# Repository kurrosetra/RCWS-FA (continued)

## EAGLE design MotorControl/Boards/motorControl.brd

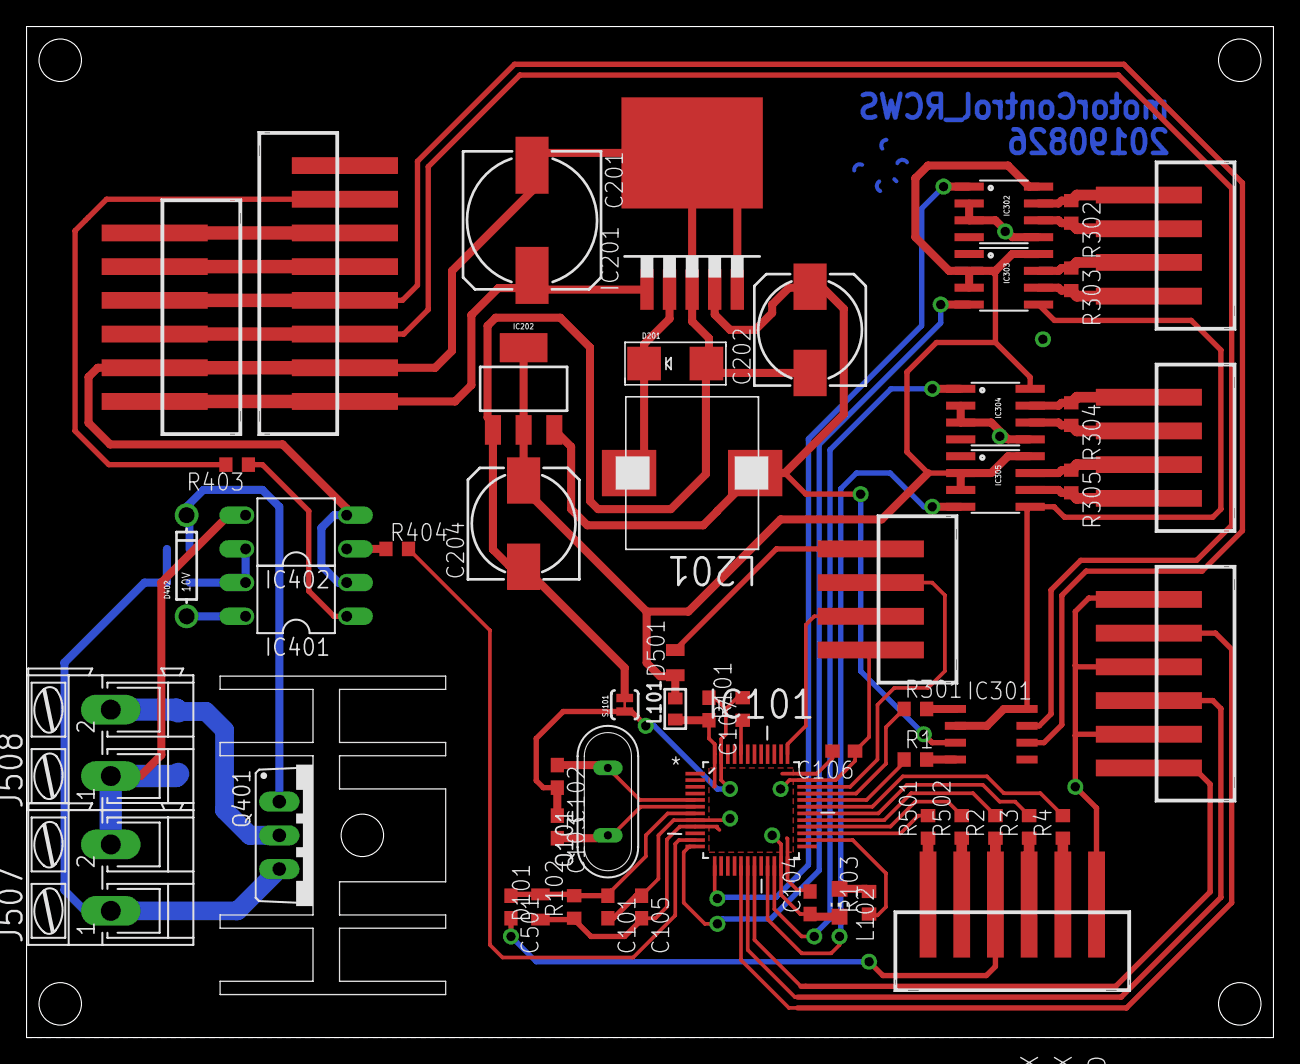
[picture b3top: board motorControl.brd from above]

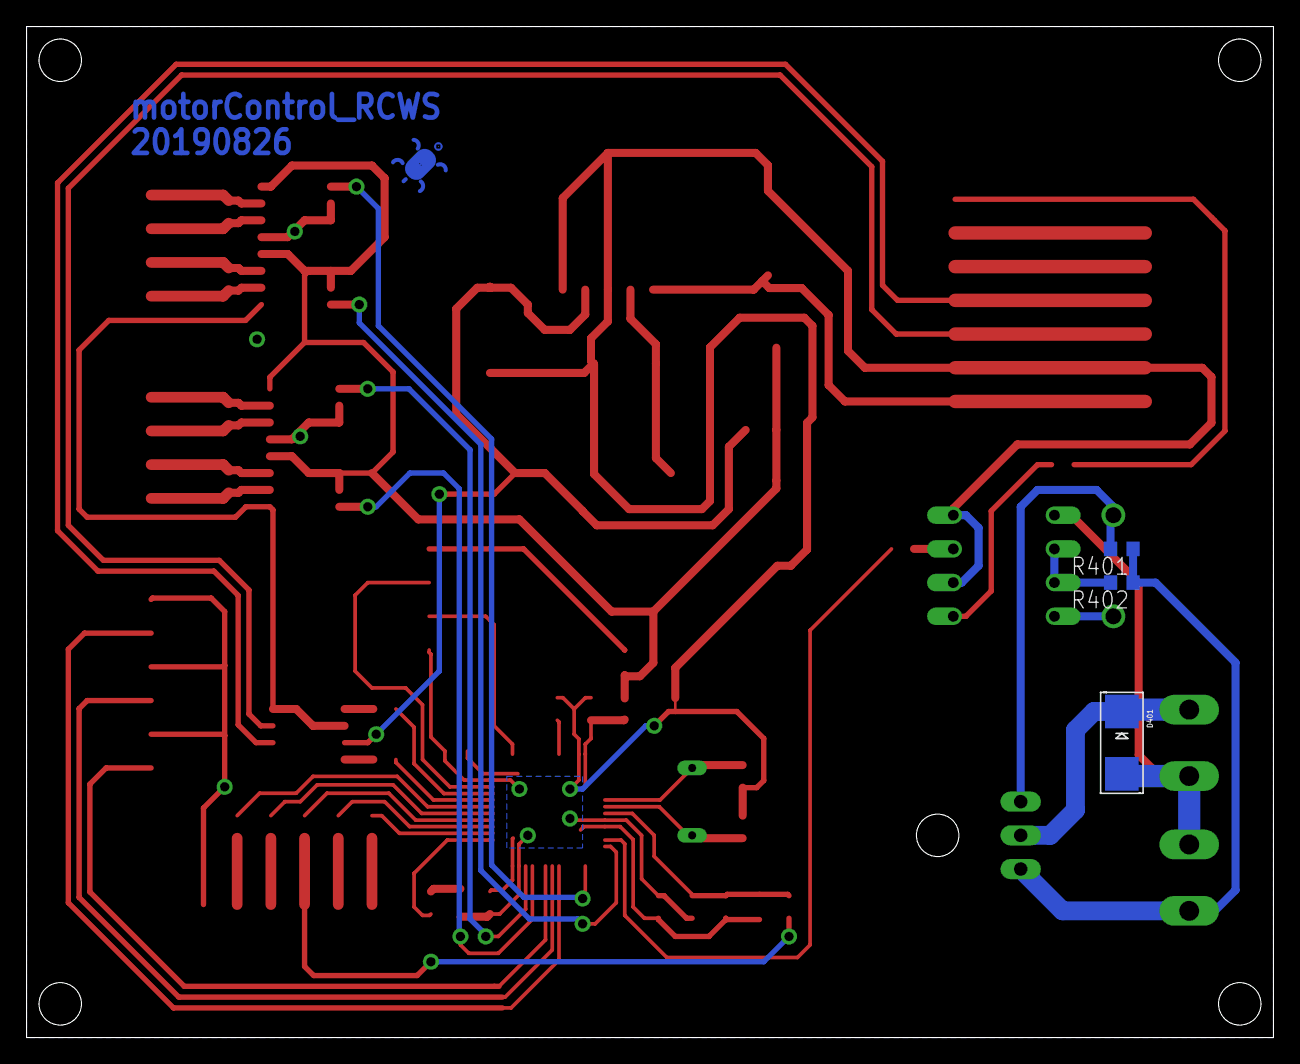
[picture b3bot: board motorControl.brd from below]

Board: 2 copper layers, 94.0 x 76.2 mm, 61 parts (3 on the bottom side), 59 nets.

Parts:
C101: 10n; C0603
C102, C103: 22p; C0603
C104, C105, C106, C107, C501: 100n; C0603
C201: 470u/35V; 153CLV-1012
C202, C204: 1000u/6V3; 153CLV-0810
D101, D501: SCHOTTKY; MICROMELF-W
D201, D401: SS34; SMADIODE
D402: 10V; DO-4148
IC101: STM32F103C8T6; QFP50P900X900X160-48N
IC201: LM2596S-5V; D2PAK
IC202: LM1117-3V3; SOT223
IC301: MCP2561-E/SN; SOIC-8
IC302, IC303, IC304, IC305: RS485SOIC; SO08
IC401, IC402: PC817; DIL04
J501: PROG; XH-4-VERT-SMD
J502: BUS; XH-8-VERT-SMD
J503: OPTRONIK; XH-6-VERT-SMD
J504: MTR_AZ_COMM; XH-4-VERT-SMD
J505: MTR_EL_COMM; XH-4-VERT-SMD
J506: LIMIT_SWITCH; XH-6-VERT-SMD
J507: POWER_IN; AK300/2
J508: TRIGGER_OUT; AK300/2
J509: COCK_DRIVER; XH-6-VERT-SMD
KK401: BV_240X170-HOLE
L101: FB_0603; L0603
L102: GREEN; CHIP-LED0805
L201: 33uH; PA4342
Q101: 8MHz; QS
Q401: IRF9530; TO220BV
R1, R2, R3, R4, R301, R302, R303, R304, R305, R501, R502: 120R; R0603
R101, R102: 100K; R0603
R103: 1k; R0603
R401: 470R; R0603
R402: 100k; R0603
R403, R404: 330R; R0603
SJ101: SJ_2S-TRACE
U$1: KURRO_FOOTPRINT; KURRO-LOGO

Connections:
+3V3: C204.+, D501.C, IC202.2, IC202.4, IC302.8, IC303.2, IC303.3, IC303.8, IC304.8, IC305.2, IC305.3, IC305.8, L101.2
+5V: C202.+, IC201.4, IC202.3, IC301.3, L201.P$2
+12V: C201.+, IC201.1, J502.1, J503.6
+24V: J507.1, Q401.S, R401.1, R402.1
AGND: C101.2, C102.2, C103.1, C104.1, C105.1, C106.1, C107.1, IC101.8, IC101.23, IC101.35, IC101.47, J501.4, L102.C, R101.2, SJ101.1
BOOT0: IC101.44, R101.1
BUS_CANH: IC301.7, J502.3, J503.4
BUS_CANL: IC301.6, J502.4, J503.3
BUS_RXD: IC101.32, R1.1
BUS_TRIGGER_PULSE: J502.7, R403.2
BUS_TXD: IC101.33, R301.1
BUS_VIDEO+: J502.5, J503.2
BUS_VIDEO-: J502.6, J503.1
COCK_ALM: IC101.31, R4.2
COCK_AWO: IC101.28, R502.2
COCK_DIR: IC101.29, R2.2
COCK_PLS: IC101.30, R3.2
COCK_POS: IC101.27, R501.2
GND: C201.-, C202.-, C204.-, D201.A, IC201.3, IC201.5, IC201.6, IC202.1, IC301.2, IC301.8, IC302.2, IC302.3, IC302.5, IC303.5, IC304.2, IC304.3, IC304.5, IC305.5, IC401.2, IC402.2, J502.2, J503.5, J506.1, J506.3, J506.5, J509.1, SJ101.2
LIM_AZ: IC101.17, J506.2
LIM_EL_DOWN: IC101.19, J506.6
LIM_EL_UP: IC101.18, J506.4
LM2596_OUT: D201.C, IC201.2, L201.P$1
MTR_AZ_RXD: IC101.13, IC302.1
MTR_AZ_RX_A: IC303.6, J504.4, R303.2
MTR_AZ_RX_B: IC303.7, J504.3, R303.1
MTR_AZ_TXD: IC101.12, IC303.4
MTR_AZ_TX_A: IC302.6, J504.2, R302.2
MTR_AZ_TX_B: IC302.7, J504.1, R302.1
MTR_EL_RXD: IC101.22, IC304.1
MTR_EL_RX_A: IC305.6, J505.4, R305.2
MTR_EL_RX_B: IC305.7, J505.3, R305.1
MTR_EL_TXD: IC101.21, IC305.4
MTR_EL_TX_A: IC304.6, J505.2, R304.2
MTR_EL_TX_B: IC304.7, J505.1, R304.1
unnamed: L102.A, R103.2
unnamed: IC101.26, R103.1
unnamed: C103.2, IC101.6, Q101.1
unnamed: C102.1, IC101.5, Q101.2
unnamed: IC301.1, R301.2
unnamed: IC301.4, R1.2
unnamed: J509.5, R502.1
unnamed: J509.6, R501.1
unnamed: C501.2, J509.4, R2.1
unnamed: J509.3, R3.1
unnamed: J509.2, R4.1
unnamed: D501.A, J501.1
unnamed: D402.C, Q401.G, R401.2
unnamed: IC401.3, IC402.4, R402.2
unnamed: IC401.1, R403.1
unnamed: IC402.1, R404.1
unnamed: D402.A, IC401.4
RST: C101.1, C501.1, D101.A, IC101.7, R102.2
SWCLK: IC101.37, J501.3
SWDIO: IC101.34, J501.2
TRIGGER+: D401.C, J508.2, Q401.D
TRIGGER_ENABLE: IC101.11, R404.2
V-: D401.A, IC402.3, J507.2, J508.1
VDD: C104.2, C105.2, C106.2, C107.2, D101.C, IC101.9, IC101.24, IC101.36, IC101.48, L101.1, R102.1

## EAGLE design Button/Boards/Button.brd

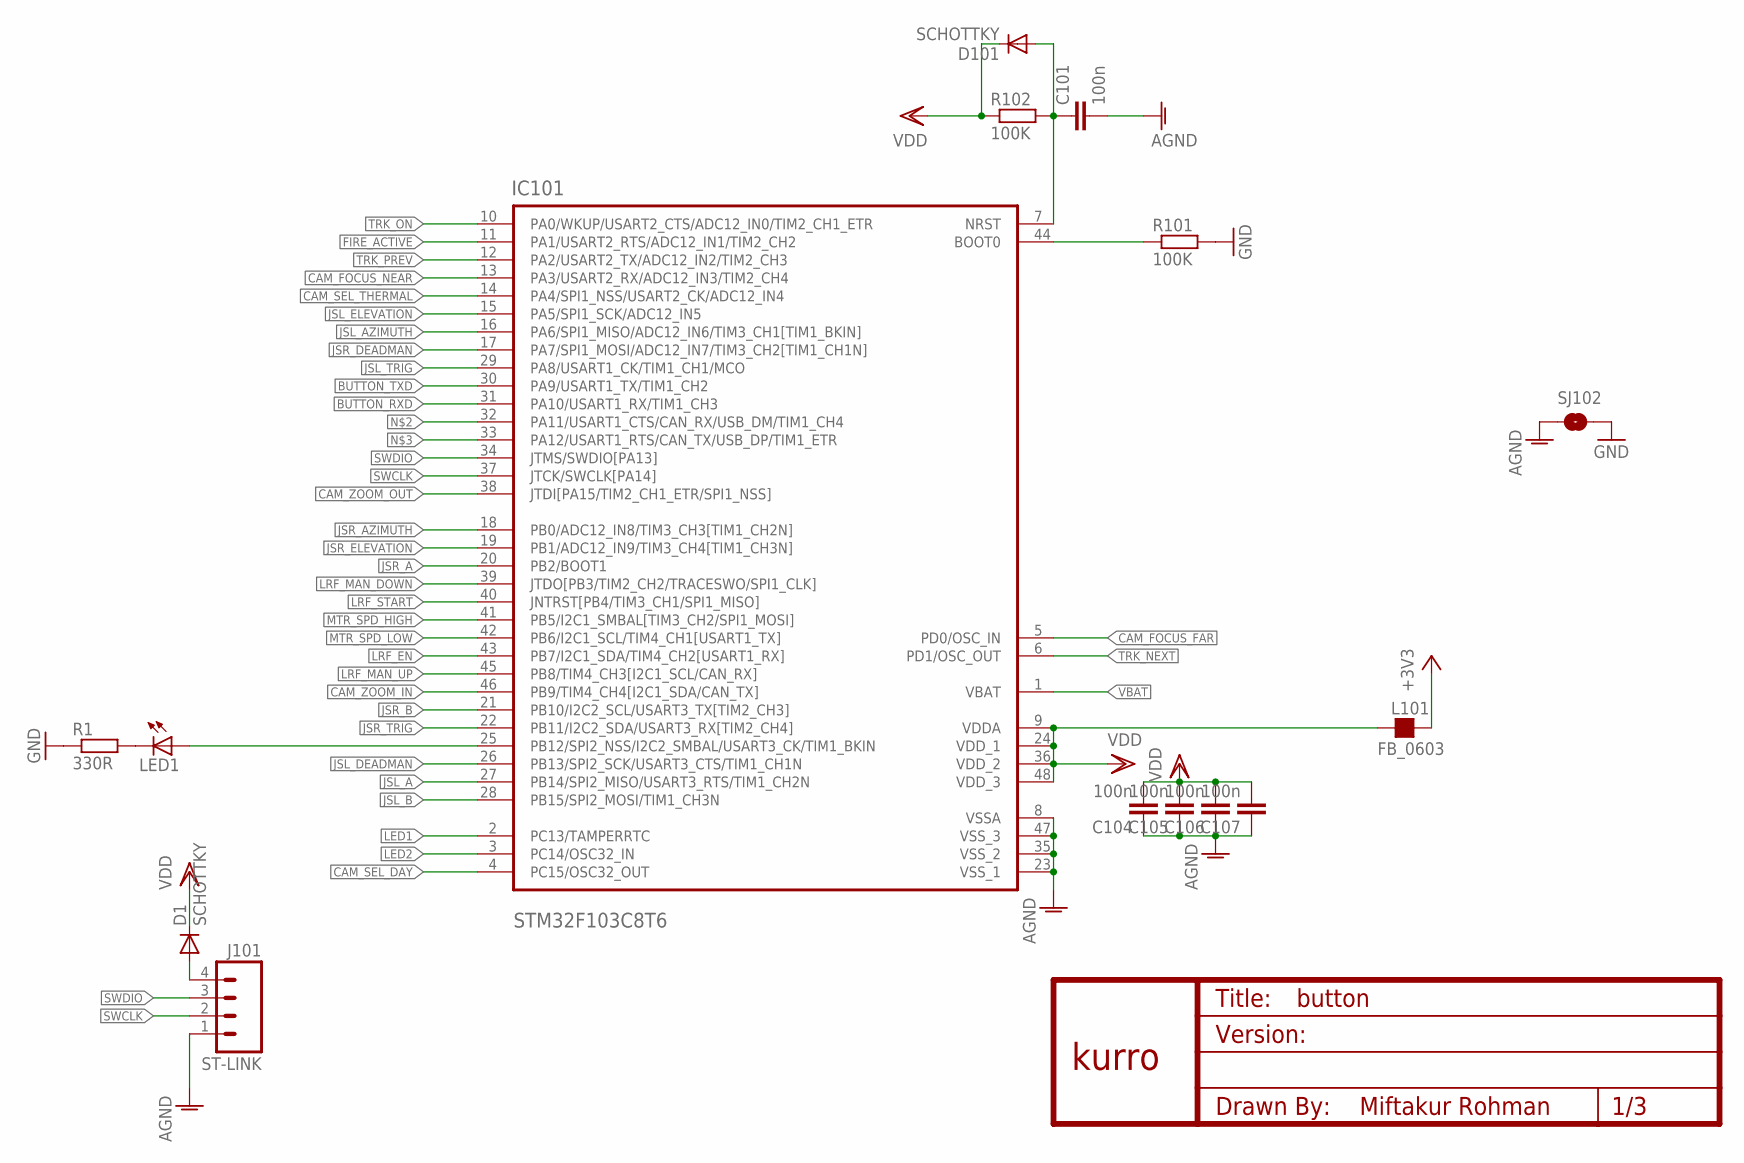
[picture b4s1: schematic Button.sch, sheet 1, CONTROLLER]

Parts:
C101, C104, C105, C106, C107: 100n; C0603
D1, D101: SCHOTTKY; MICROMELF-W
IC101: STM32F103C8T6; QFP50P900X900X160-48N
J101: ST-LINK; XH-4-VERT
L101: FB_0603; L0603
LED1: LED-3MM-NO_SILK; LED3MM-NS
R1: 330R; R0603
R101, R102: 100K; R0603
SJ102: SOLDERJUMPERTRACE; SJ_2S-TRACE
U$1: KURRO_FOOTPRINT; KURRO-LOGO

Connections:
+3V3: L101.2; also elsewhere on the board
AGND: C101.2, C104.1, C105.1, C106.1, C107.1, IC101.8 (VSSA), IC101.23 (VSS_1), IC101.35 (VSS_2), IC101.47 (VSS_3), J101.1, SJ102.1
BOOT0: IC101.44 (BOOT0), R101.1
BUTTON_RXD: IC101.31 (PA10/USART1_RX/TIM1_CH3); also elsewhere on the board
BUTTON_TXD: IC101.30 (PA9/USART1_TX/TIM1_CH2); also elsewhere on the board
CAM_FOCUS_FAR: IC101.5 (PD0/OSC_IN); also elsewhere on the board
CAM_FOCUS_NEAR: IC101.13 (PA3/USART2_RX/ADC12_IN3/TIM2_CH4); also elsewhere on the board
CAM_SEL_DAY: IC101.4 (PC15/OSC32_OUT); also elsewhere on the board
CAM_SEL_THERMAL: IC101.14 (PA4/SPI1_NSS/USART2_CK/ADC12_IN4); also elsewhere on the board
CAM_ZOOM_IN: IC101.46 (PB9/TIM4_CH4[I2C1_SDA/CAN_TX]); also elsewhere on the board
CAM_ZOOM_OUT: IC101.38 (JTDI[PA15/TIM2_CH1_ETR/SPI1_NSS]); also elsewhere on the board
FIRE_ACTIVE: IC101.11 (PA1/USART2_RTS/ADC12_IN1/TIM2_CH2); also elsewhere on the board
GND: R1.1, R101.2, SJ102.2; also elsewhere on the board
JSL_A: IC101.27 (PB14/SPI2_MISO/USART3_RTS/TIM1_CH2N); also elsewhere on the board
JSL_AZIMUTH: IC101.16 (PA6/SPI1_MISO/ADC12_IN6/TIM3_CH1[TIM1_B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); also elsewhere on the board
JSL_B: IC101.28 (PB15/SPI2_MOSI/TIM1_CH3N); also elsewhere on the board
JSL_DEADMAN: IC101.26 (PB13/SPI2_SCK/USART3_CTS/TIM1_CH1N); also elsewhere on the board
JSL_ELEVATION: IC101.15 (PA5/SPI1_SCK/ADC12_IN5); also elsewhere on the board
JSL_TRIG: IC101.29 (PA8/USART1_CK/TIM1_CH1/MCO); also elsewhere on the board
JSR_A: IC101.20 (PB2/BOOT1); also elsewhere on the board
JSR_AZIMUTH: IC101.18 (PB0/ADC12_IN8/TIM3_CH3[TIM1_CH2N]); also elsewhere on the board
JSR_B: IC101.21 (PB10/I2C2_SCL/USART3_TX[TIM2_CH3]); also elsewhere on the board
JSR_DEADMAN: IC101.17 (PA7/SPI1_MOSI/ADC12_IN7/TIM3_CH2[TIM1_C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); also elsewhere on the board
JSR_ELEVATION: IC101.19 (PB1/ADC12_IN9/TIM3_CH4[TIM1_CH3N]); also elsewhere on the board
JSR_TRIG: IC101.22 (PB11/I2C2_SDA/USART3_RX[TIM2_CH4]); also elsewhere on the board
LED1: IC101.2 (PC13/TAMPERRTC); also elsewhere on the board
LED2: IC101.3 (PC14/OSC32_IN); also elsewhere on the board
LRF_EN: IC101.43 (PB7/I2C1_SDA/TIM4_CH2[USART1_RX]); also elsewhere on the board
LRF_MAN_DOWN: IC101.39 (JTDO[PB3/TIM2_CH2/TRACESWO/SPI1_CLK]); also elsewhere on the board
LRF_MAN_UP: IC101.45 (PB8/TIM4_CH3[I2C1_SCL/CAN_RX]); also elsewhere on the board
LRF_START: IC101.40 (JNTRST[PB4/TIM3_CH1/SPI1_MISO]); also elsewhere on the board
MTR_SPD_HIGH: IC101.41 (PB5/I2C1_SMBAL[TIM3_CH2/SPI1_MOSI]); also elsewhere on the board
MTR_SPD_LOW: IC101.42 (PB6/I2C1_SCL/TIM4_CH1[USART1_TX]); also elsewhere on the board
unnamed: IC101.25 (PB12/SPI2_NSS/I2C2_SMBAL/USART3_CK/TIM1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), LED1.A
unnamed: D1.A, J101.4
unnamed: LED1.K (C), R1.2
RST: C101.1, D101.A, IC101.7 (NRST), R102.2
SWCLK: IC101.37 (JTCK/SWCLK[PA14]), J101.2
SWDIO: IC101.34 (JTMS/SWDIO[PA13]), J101.3
TRK_NEXT: IC101.6 (PD1/OSC_OUT); also elsewhere on the board
TRK_ON: IC101.10 (PA0/WKUP/USART2_CTS/ADC12_IN0/TIM2_CH1_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); also elsewhere on the board
TRK_PREV: IC101.12 (PA2/USART2_TX/ADC12_IN2/TIM2_CH3); also elsewhere on the board
VBAT: IC101.1 (VBAT)
VDD: C104.2, C105.2, C106.2, C107.2, D1.C, D101.C, IC101.9 (VDDA), IC101.24 (VDD_1), IC101.36 (VDD_2), IC101.48 (VDD_3), L101.1, R102.1

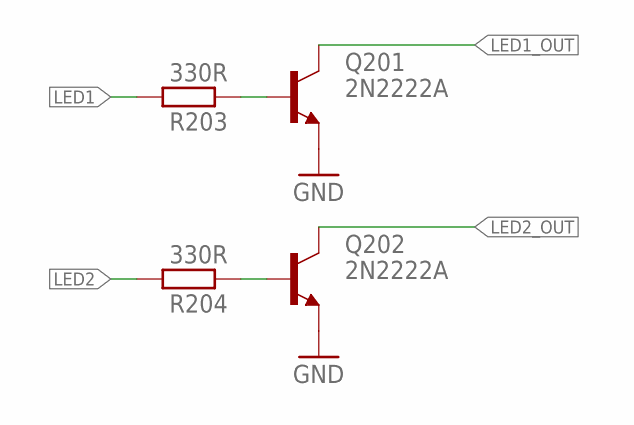
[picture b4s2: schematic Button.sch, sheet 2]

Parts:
Q201, Q202: 2N2222A; SOT23
R203, R204: 330R; R0603

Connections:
GND: Q201.2 (E), Q202.2 (E); also elsewhere on the board
LED1: R203.2; also elsewhere on the board
LED1_OUT: Q201.3 (C); also elsewhere on the board
LED2: R204.2; also elsewhere on the board
LED2_OUT: Q202.3 (C); also elsewhere on the board
unnamed: Q201.1 (B), R203.1
unnamed: Q202.1 (B), R204.1

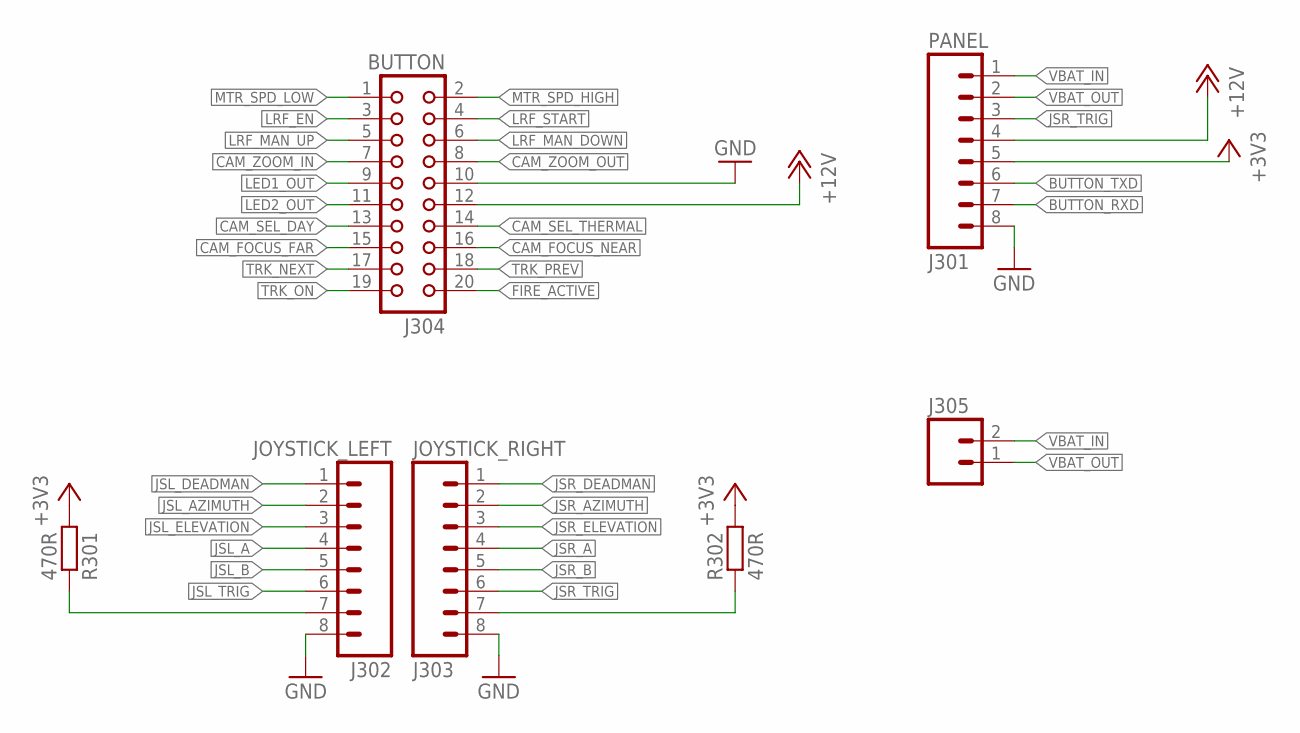
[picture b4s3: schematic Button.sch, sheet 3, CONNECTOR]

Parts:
J301: PANEL; XH-8-RA
J302: JOYSTICK_LEFT; XH-8-RA
J303: JOYSTICK_RIGHT; XH-8-RA
J304: BUTTON; CON20
J305: M02-XH-RA; XH-2-RA
R301, R302: 470R; R0603

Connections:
+3V3: J301.5, R301.2, R302.2; also elsewhere on the board
+12V: J301.4, J304.12
BUTTON_RXD: J301.7; also elsewhere on the board
BUTTON_TXD: J301.6; also elsewhere on the board
CAM_FOCUS_FAR: J304.15; also elsewhere on the board
CAM_FOCUS_NEAR: J304.16; also elsewhere on the board
CAM_SEL_DAY: J304.13; also elsewhere on the board
CAM_SEL_THERMAL: J304.14; also elsewhere on the board
CAM_ZOOM_IN: J304.7; also elsewhere on the board
CAM_ZOOM_OUT: J304.8; also elsewhere on the board
FIRE_ACTIVE: J304.20; also elsewhere on the board
GND: J301.8, J302.8, J303.8, J304.10; also elsewhere on the board
JSL_A: J302.4; also elsewhere on the board
JSL_AZIMUTH: J302.2; also elsewhere on the board
JSL_B: J302.5; also elsewhere on the board
JSL_DEADMAN: J302.1; also elsewhere on the board
JSL_ELEVATION: J302.3; also elsewhere on the board
JSL_TRIG: J302.6; also elsewhere on the board
JSR_A: J303.4; also elsewhere on the board
JSR_AZIMUTH: J303.2; also elsewhere on the board
JSR_B: J303.5; also elsewhere on the board
JSR_DEADMAN: J303.1; also elsewhere on the board
JSR_ELEVATION: J303.3; also elsewhere on the board
JSR_TRIG: J301.3, J303.6; also elsewhere on the board
LED1_OUT: J304.9; also elsewhere on the board
LED2_OUT: J304.11; also elsewhere on the board
LRF_EN: J304.3; also elsewhere on the board
LRF_MAN_DOWN: J304.6; also elsewhere on the board
LRF_MAN_UP: J304.5; also elsewhere on the board
LRF_START: J304.4; also elsewhere on the board
MTR_SPD_HIGH: J304.2; also elsewhere on the board
MTR_SPD_LOW: J304.1; also elsewhere on the board
unnamed: J303.7, R302.1
unnamed: J302.7, R301.1
TRK_NEXT: J304.17; also elsewhere on the board
TRK_ON: J304.19; also elsewhere on the board
TRK_PREV: J304.18; also elsewhere on the board
VBAT_IN: J301.1, J305.2
VBAT_OUT: J301.2, J305.1

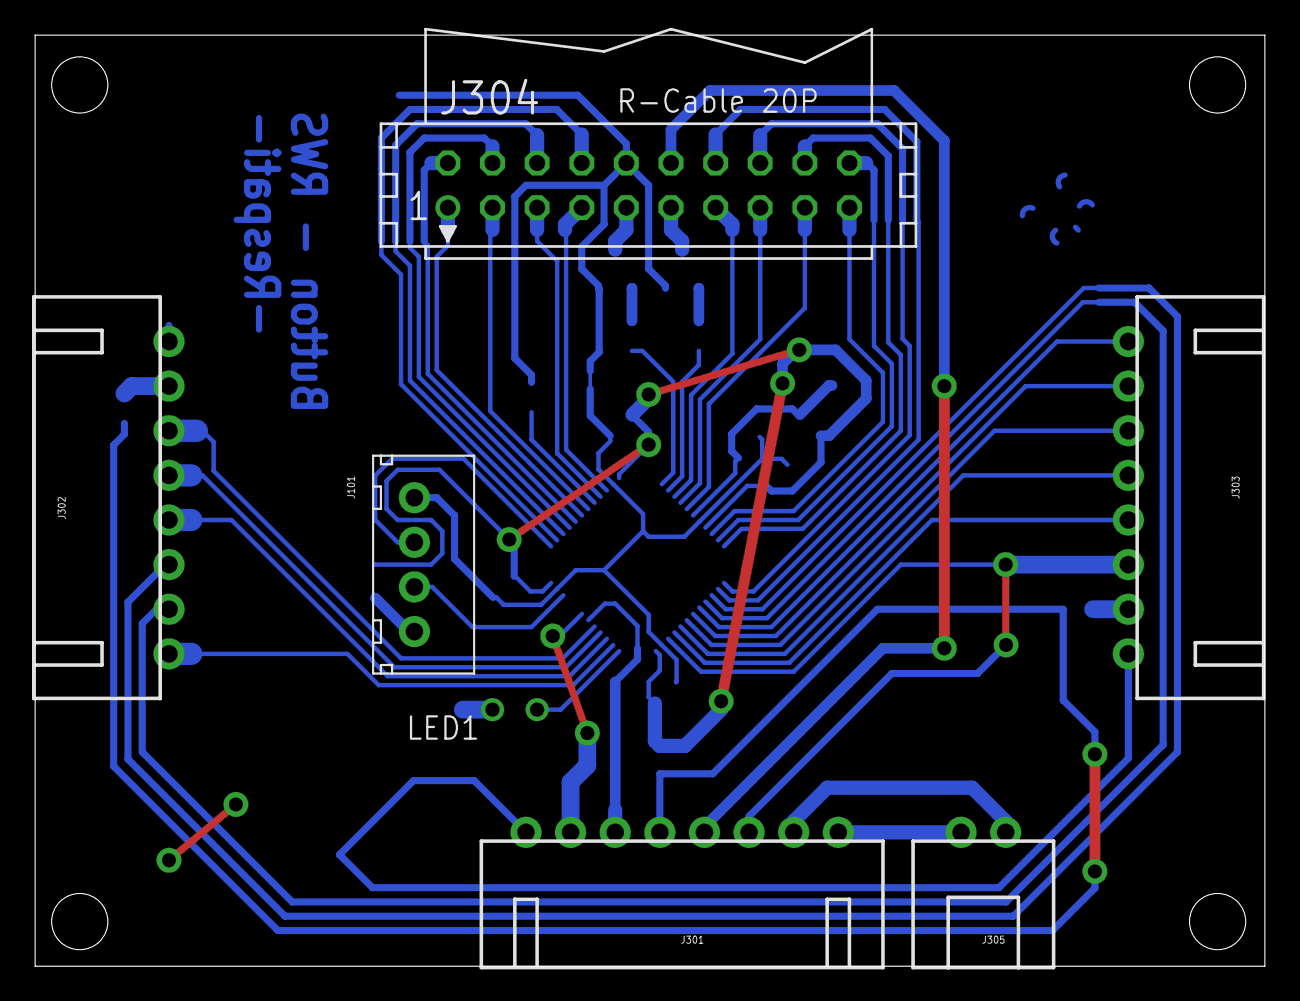
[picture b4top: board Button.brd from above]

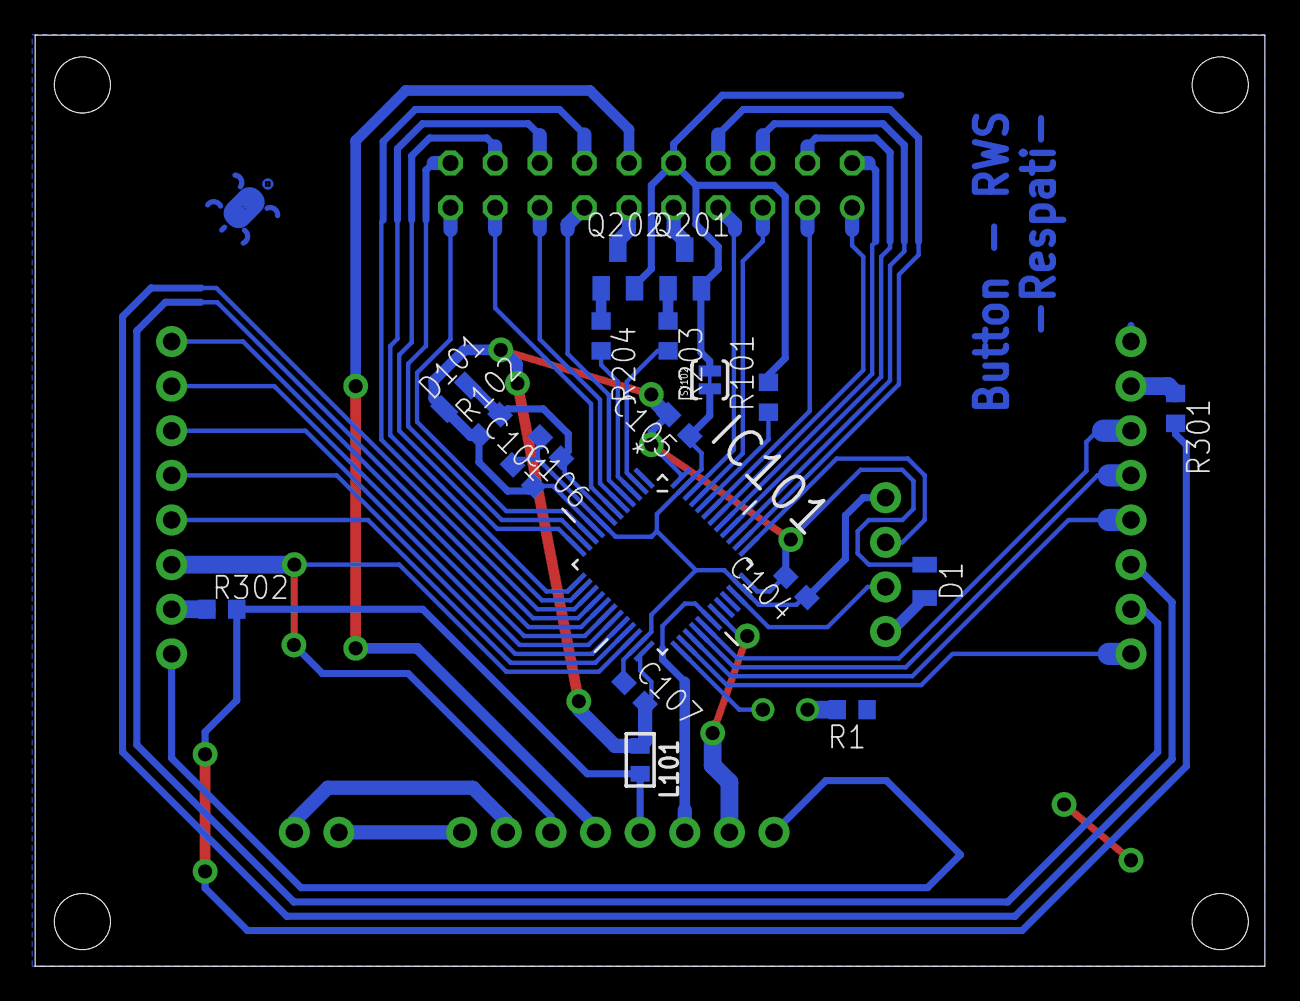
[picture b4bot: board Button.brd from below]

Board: 2 copper layers, 70.0 x 53.0 mm, 27 parts (19 on the bottom side), 52 nets.

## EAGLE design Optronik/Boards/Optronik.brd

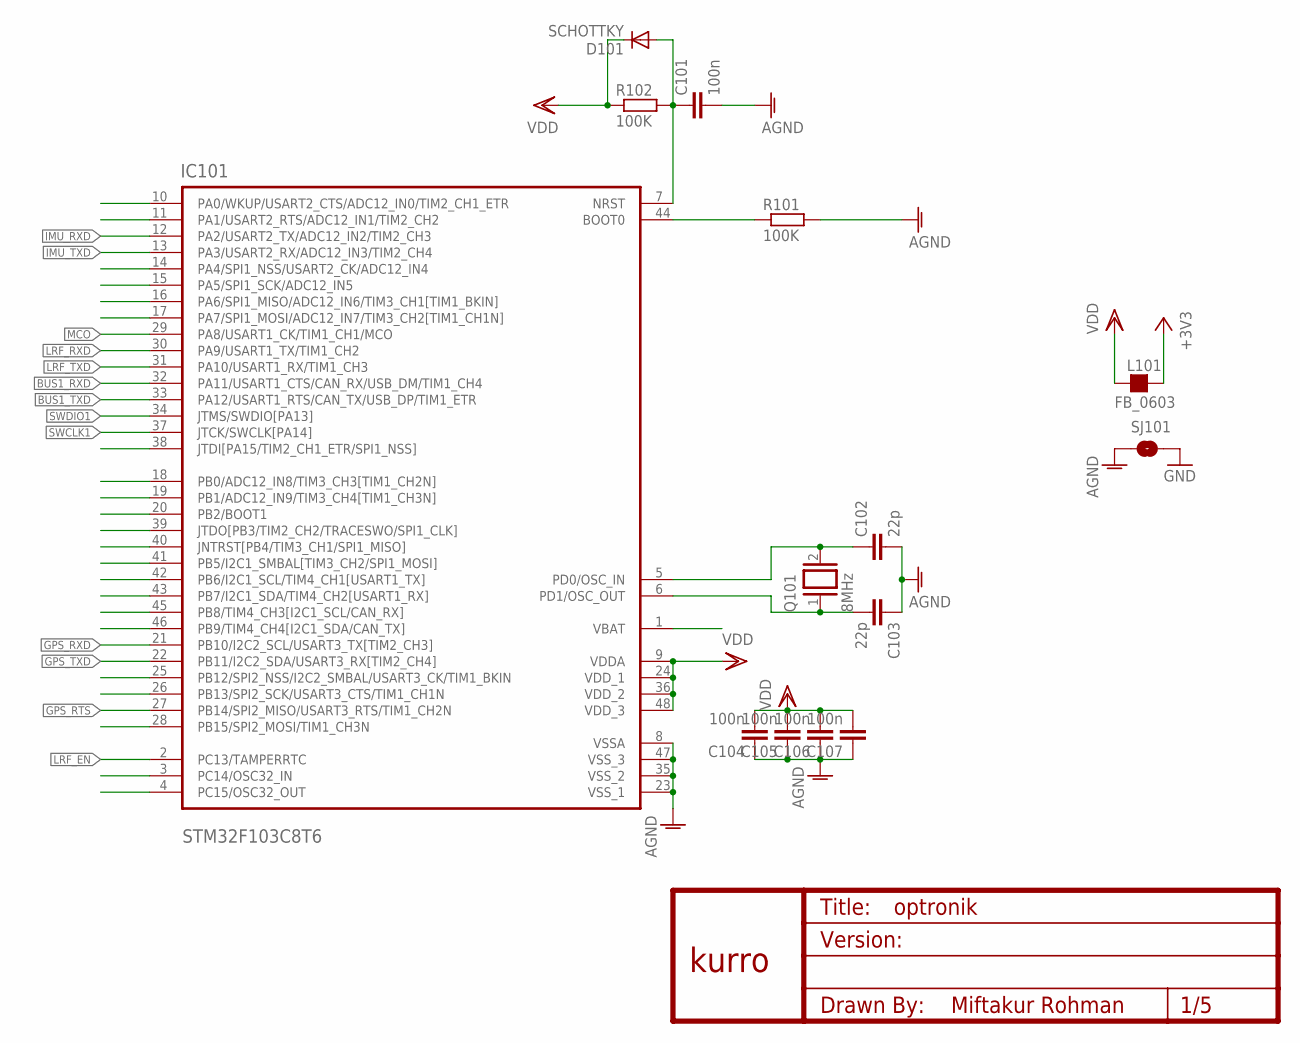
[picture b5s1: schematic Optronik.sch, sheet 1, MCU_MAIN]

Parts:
C101, C104, C105, C106, C107: 100n; C0603
C102, C103: 22p; C0603
D101: SCHOTTKY; MICROMELF-W
IC101: STM32F103C8T6; QFP50P900X900X160-48N
L101: FB_0603; L0603
Q101: 8MHz; QS
R101, R102: 100K; R0603
SJ101: SOLDERJUMPERTRACE; SJ_2S-TRACE
U$1: KURRO_FOOTPRINT; KURRO-LOGO

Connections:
+3V3: L101.2; also elsewhere on the board
AGND: C101.2, C102.2, C103.1, C104.1, C105.1, C106.1, C107.1, IC101.8 (VSSA), IC101.23 (VSS_1), IC101.35 (VSS_2), IC101.47 (VSS_3), R101.2, SJ101.1
BOOT0: IC101.44 (BOOT0), R101.1
BUS1_RXD: IC101.32 (PA11/USART1_CTS/CAN_RX/USB_DM/TIM1_CH4); also elsewhere on the board
BUS1_TXD: IC101.33 (PA12/USART1_RTS/CAN_TX/USB_DP/TIM1_ETR); also elsewhere on the board
GND: SJ101.2; also elsewhere on the board
GPS_RTS: IC101.27 (PB14/SPI2_MISO/USART3_RTS/TIM1_CH2N); also elsewhere on the board
GPS_RXD: IC101.21 (PB10/I2C2_SCL/USART3_TX[TIM2_CH3]); also elsewhere on the board
GPS_TXD: IC101.22 (PB11/I2C2_SDA/USART3_RX[TIM2_CH4]); also elsewhere on the board
IMU_RXD: IC101.12 (PA2/USART2_TX/ADC12_IN2/TIM2_CH3); also elsewhere on the board
IMU_TXD: IC101.13 (PA3/USART2_RX/ADC12_IN3/TIM2_CH4); also elsewhere on the board
LRF_EN: IC101.2 (PC13/TAMPERRTC); also elsewhere on the board
LRF_RXD: IC101.30 (PA9/USART1_TX/TIM1_CH2); also elsewhere on the board
LRF_TXD: IC101.31 (PA10/USART1_RX/TIM1_CH3); also elsewhere on the board
MCO: IC101.29 (PA8/USART1_CK/TIM1_CH1/MCO); also elsewhere on the board
unnamed: C103.2, IC101.6 (PD1/OSC_OUT), Q101.1
unnamed: C102.1, IC101.5 (PD0/OSC_IN), Q101.2
RST: C101.1, D101.A, IC101.7 (NRST), R102.2
SWCLK1: IC101.37 (JTCK/SWCLK[PA14]); also elsewhere on the board
SWDIO1: IC101.34 (JTMS/SWDIO[PA13]); also elsewhere on the board
VDD: C104.2, C105.2, C106.2, C107.2, D101.C, IC101.9 (VDDA), IC101.24 (VDD_1), IC101.36 (VDD_2), IC101.48 (VDD_3), L101.1, R102.1; also elsewhere on the board

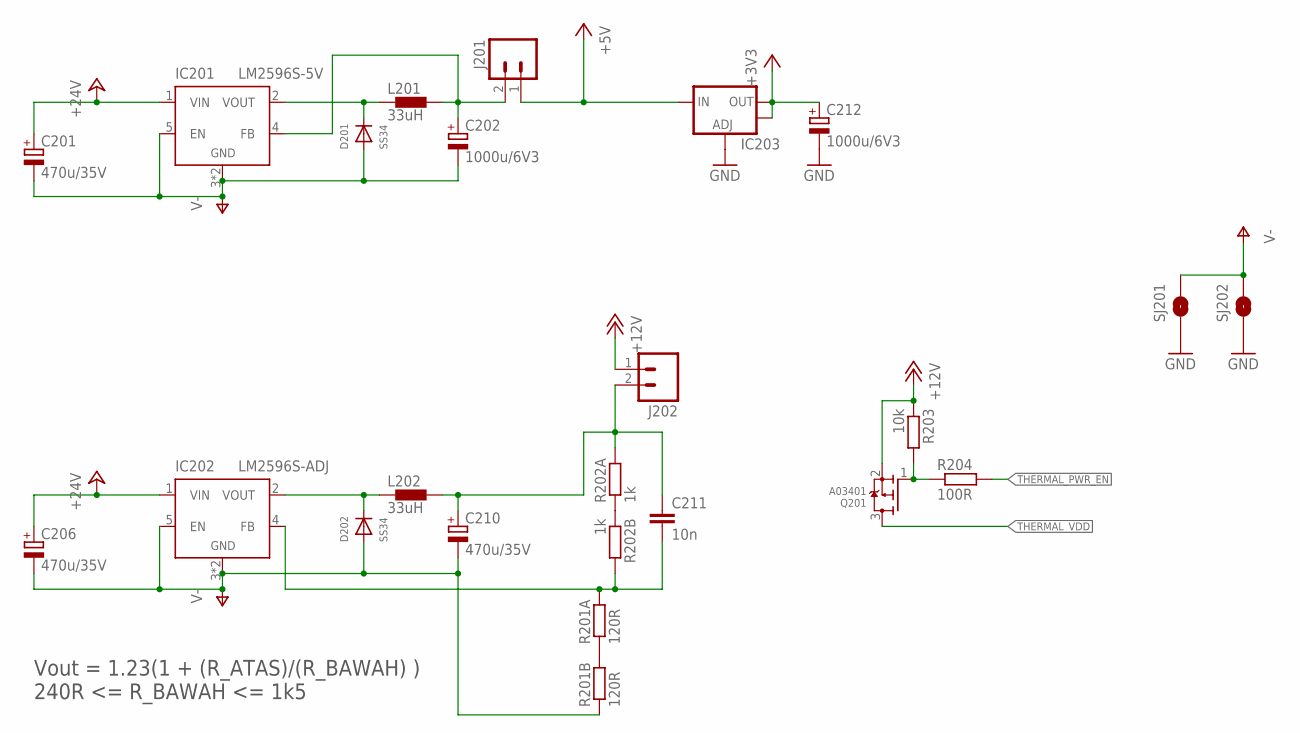
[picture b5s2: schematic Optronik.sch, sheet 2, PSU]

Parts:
C201, C206, C210: 470u/35V; 153CLV-1012
C202, C212: 1000u/6V3; 153CLV-0810
C211: 10n; C0603
D201, D202: SS34; SMADIODE
IC201: LM2596S-5V; D2PAK
IC202: LM2596S-ADJ; D2PAK
IC203: V_REG_LM1117SOT223; SOT223
J201, J202: M02-XH-VERT-SMD; XH-2-VERT-SMD
L201, L202: 33uH; PA4342
Q201: A03401; SOT23-W
R201A, R201B: 120R; R0603
R202A, R202B: 1k; R0603
R203: 10k; R0603
R204: 100R; R0603
SJ201, SJ202: SOLDERJUMPERTRACE; SJ_2S-TRACE

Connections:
+3V3: C212.+, IC203.2 (OUT), IC203.4 (OUT); also elsewhere on the board
+5V: IC203.3 (IN), J201.1; also elsewhere on the board
+12V: J202.1, Q201.2 (S), R203.1; also elsewhere on the board
+24V: C201.+, C206.+, IC201.1 (VIN), IC202.1 (VIN); also elsewhere on the board
FEED1: C211.2, IC202.4 (FB), R201A.2, R202B.2
GND: C212.-, IC203.1 (ADJ), SJ201.1, SJ202.1; also elsewhere on the board
unnamed: D201.C, IC201.2 (VOUT), L201.P$1 (1)
unnamed: D202.C, IC202.2 (VOUT), L202.P$1 (1)
unnamed: R201A.1, R201B.2
unnamed: R202A.1, R202B.1
unnamed: C202.+, IC201.4 (FB), J201.2, L201.P$2 (2)
unnamed: Q201.1 (G), R203.2, R204.1
unnamed: C210.+, C211.1, J202.2, L202.P$2 (2), R202A.2
THERMAL_PWR_EN: R204.2; also elsewhere on the board
THERMAL_VDD: Q201.3 (D); also elsewhere on the board
V-: C201.-, C202.-, C206.-, C210.-, D201.A, D202.A, IC201.3 (GND), IC201.5 (EN), IC201.6 (GND), IC202.3 (GND), IC202.5 (EN), IC202.6 (GND), R201B.1, SJ201.2, SJ202.2; also elsewhere on the board

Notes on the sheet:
Vout = 1.23(1 + (R_ATAS)/(R_BAWAH) ) 240R <= R_BAWAH <= 1k5

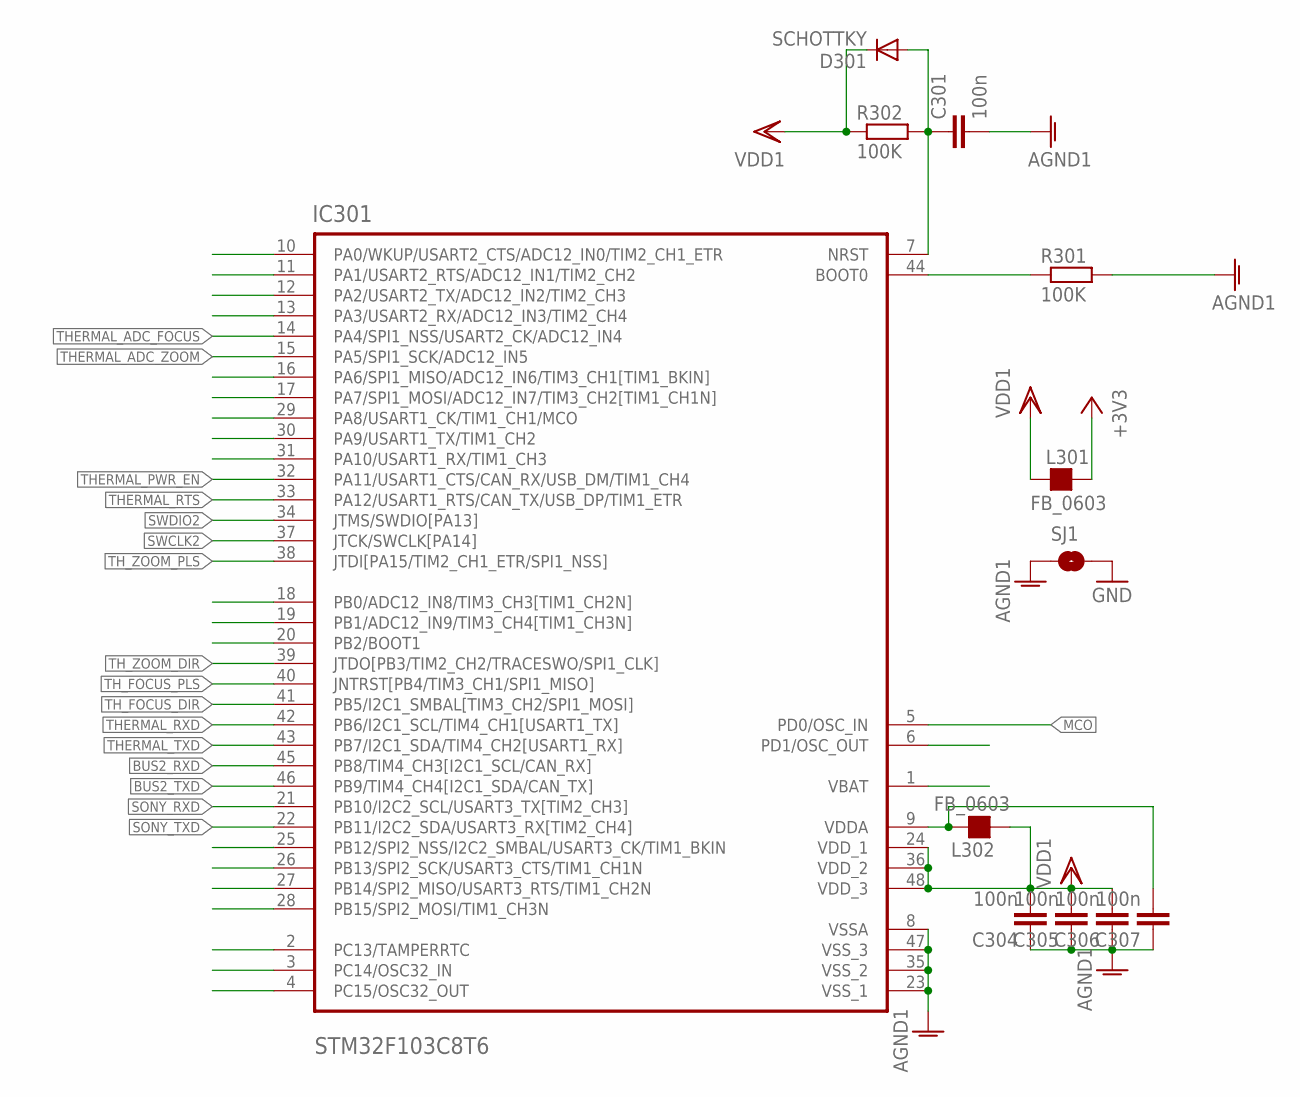
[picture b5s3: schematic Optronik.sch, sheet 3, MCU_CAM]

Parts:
C301, C304, C305, C306, C307: 100n; C0603
D301: SCHOTTKY; MICROMELF-W
IC301: STM32F103C8T6; QFP50P900X900X160-48N
L301, L302: FB_0603; L0603
R301, R302: 100K; R0603
SJ1: SOLDERJUMPERTRACE; SJ_2S-TRACE

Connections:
+3V3: L301.2; also elsewhere on the board
AGND1: C301.2, C304.1, C305.1, C306.1, C307.1, IC301.8 (VSSA), IC301.23 (VSS_1), IC301.35 (VSS_2), IC301.47 (VSS_3), R301.2, SJ1.1; also elsewhere on the board
BOOT1: IC301.44 (BOOT0), R301.1
BUS2_RXD: IC301.45 (PB8/TIM4_CH3[I2C1_SCL/CAN_RX]); also elsewhere on the board
BUS2_TXD: IC301.46 (PB9/TIM4_CH4[I2C1_SDA/CAN_TX]); also elsewhere on the board
GND: SJ1.2; also elsewhere on the board
MCO: IC301.5 (PD0/OSC_IN); also elsewhere on the board
RST1: C301.1, D301.A, IC301.7 (NRST), R302.2
SONY_RXD: IC301.21 (PB10/I2C2_SCL/USART3_TX[TIM2_CH3]); also elsewhere on the board
SONY_TXD: IC301.22 (PB11/I2C2_SDA/USART3_RX[TIM2_CH4]); also elsewhere on the board
SWCLK2: IC301.37 (JTCK/SWCLK[PA14]); also elsewhere on the board
SWDIO2: IC301.34 (JTMS/SWDIO[PA13]); also elsewhere on the board
THERMAL_ADC_FOCUS: IC301.14 (PA4/SPI1_NSS/USART2_CK/ADC12_IN4); also elsewhere on the board
THERMAL_ADC_ZOOM: IC301.15 (PA5/SPI1_SCK/ADC12_IN5); also elsewhere on the board
THERMAL_PWR_EN: IC301.32 (PA11/USART1_CTS/CAN_RX/USB_DM/TIM1_CH4); also elsewhere on the board
THERMAL_RTS: IC301.33 (PA12/USART1_RTS/CAN_TX/USB_DP/TIM1_ETR); also elsewhere on the board
THERMAL_RXD: IC301.42 (PB6/I2C1_SCL/TIM4_CH1[USART1_TX]); also elsewhere on the board
THERMAL_TXD: IC301.43 (PB7/I2C1_SDA/TIM4_CH2[USART1_RX]); also elsewhere on the board
TH_FOCUS_DIR: IC301.41 (PB5/I2C1_SMBAL[TIM3_CH2/SPI1_MOSI]); also elsewhere on the board
TH_FOCUS_PLS: IC301.40 (JNTRST[PB4/TIM3_CH1/SPI1_MISO]); also elsewhere on the board
TH_ZOOM_DIR: IC301.39 (JTDO[PB3/TIM2_CH2/TRACESWO/SPI1_CLK]); also elsewhere on the board
TH_ZOOM_PLS: IC301.38 (JTDI[PA15/TIM2_CH1_ETR/SPI1_NSS]); also elsewhere on the board
VDD1: C304.2, C305.2, C306.2, D301.C, IC301.24 (VDD_1), IC301.36 (VDD_2), IC301.48 (VDD_3), L301.1, L302.1, R302.1; also elsewhere on the board
VDDA1: C307.2, IC301.9 (VDDA), L302.2
